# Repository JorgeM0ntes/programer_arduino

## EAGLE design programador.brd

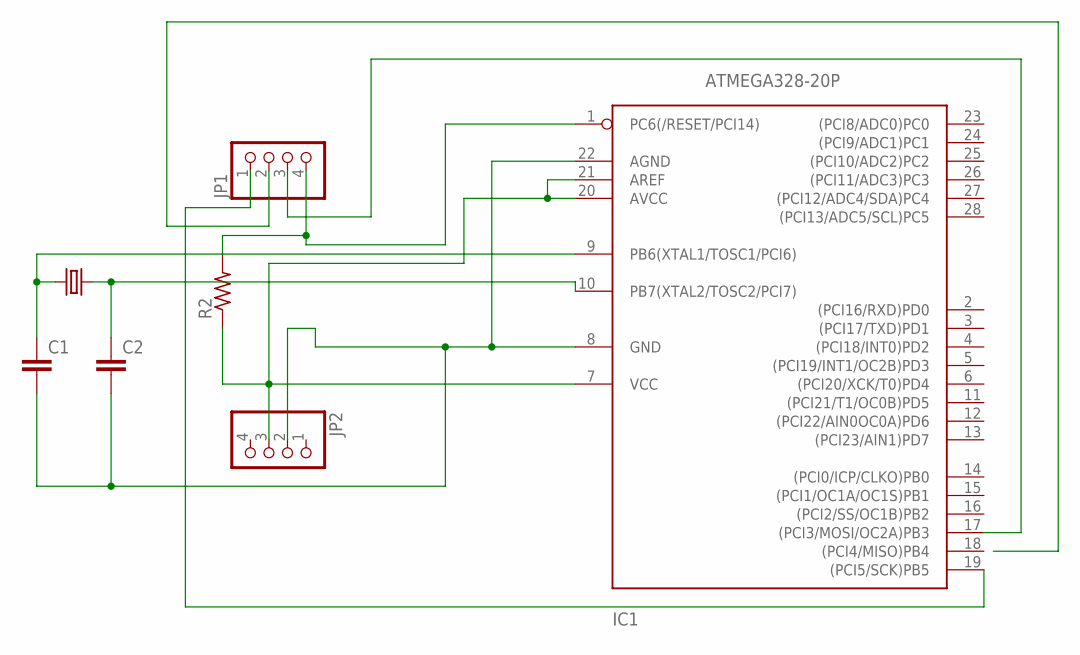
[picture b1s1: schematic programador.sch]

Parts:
C1, C2: C5/3.5; C5B3.5
IC1: ATMEGA328-20P; DIL28-3
JP1, JP2: PINHD-1X4; 1X04
Q1: CRYSTALHC49S; HC49/S
R2: R-US_0207/10; 0207/10

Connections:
GND: C1.2, C2.2, IC1.8 (GND), IC1.22 (AGND), JP2.2
unnamed: IC1.7 (VCC), IC1.20 (AVCC), IC1.21 (AREF), JP2.3, R2.1
unnamed: IC1.19 ((PCI5/SCK)PB5), JP1.1
unnamed: IC1.1 (PC6(/RESET/PCI14)), JP1.4, R2.2
unnamed: C2.1, IC1.10 (PB7(XTAL2/TOSC2/PCI7)), Q1.2
unnamed: C1.1, IC1.9 (PB6(XTAL1/TOSC1/PCI6)), Q1.1
unnamed: IC1.17 ((PCI3/MOSI/OC2A)PB3), JP1.3

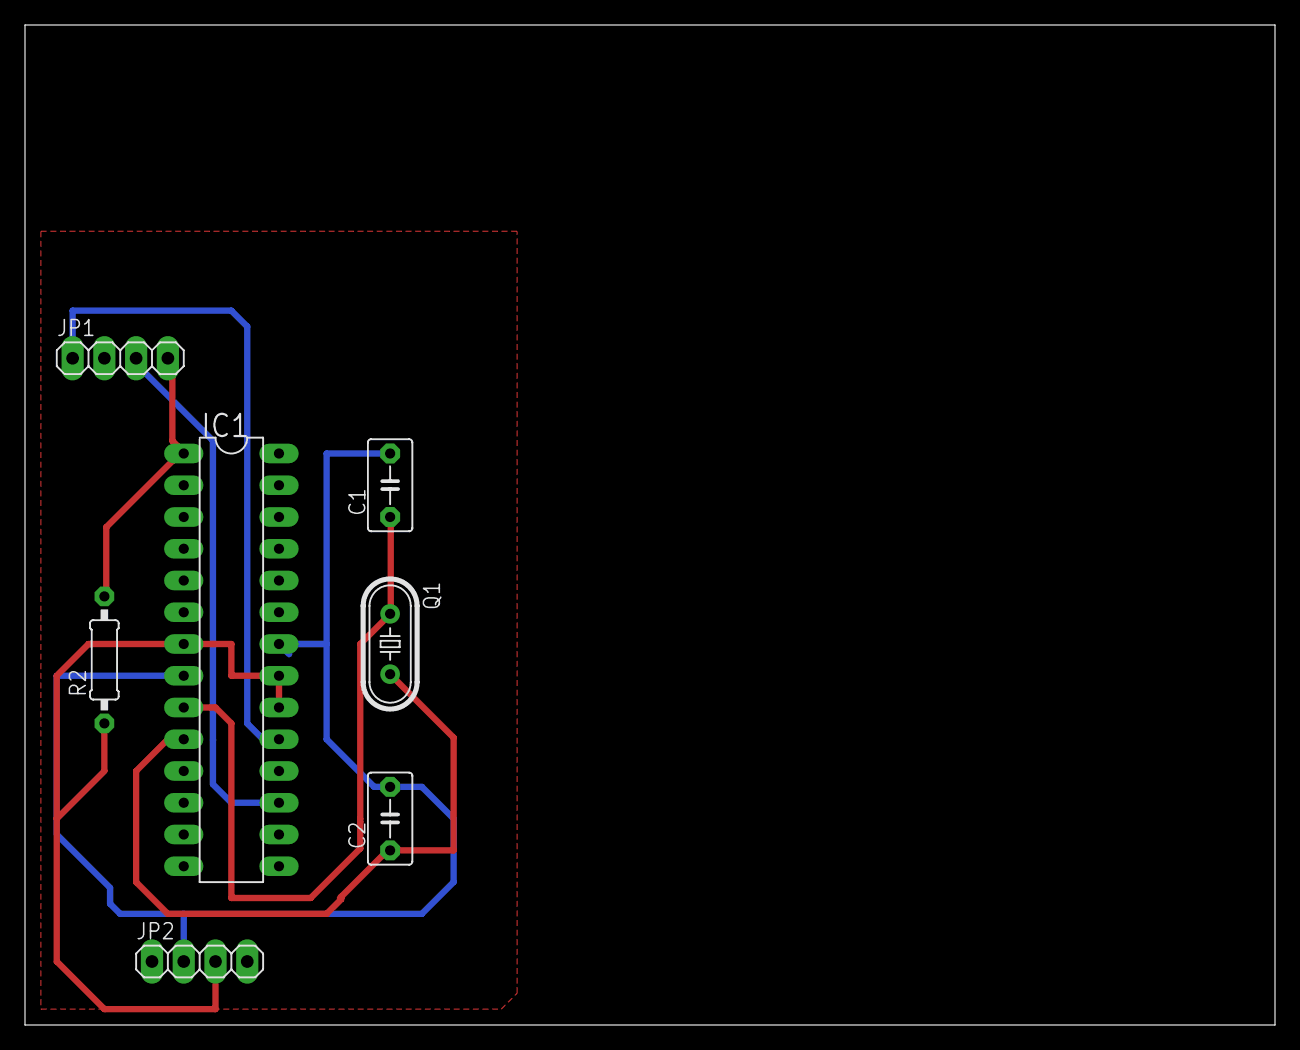
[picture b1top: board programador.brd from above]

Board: 2 copper layers, 100.0 x 80.0 mm, 7 parts (0 on the bottom side), 7 nets.

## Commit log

2020-07-25 programer
